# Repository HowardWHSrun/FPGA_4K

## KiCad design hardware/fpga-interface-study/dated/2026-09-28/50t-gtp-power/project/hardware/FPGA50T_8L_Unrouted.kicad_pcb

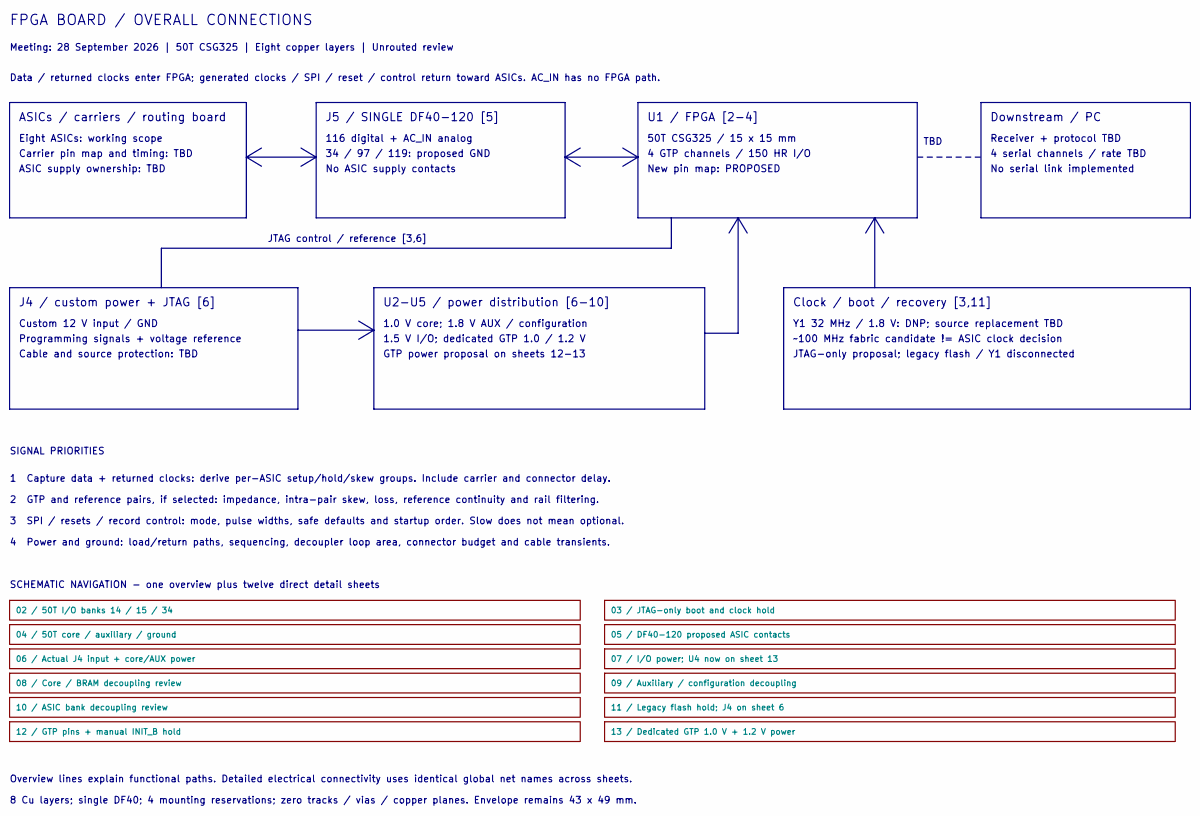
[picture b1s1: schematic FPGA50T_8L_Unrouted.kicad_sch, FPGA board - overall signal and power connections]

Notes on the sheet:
FPGA BOARD / OVERALL CONNECTIONS
Meeting: 28 September 2026 | 50T CSG325 | Eight copper layers | Unrouted review
Data / returned clocks enter FPGA; generated clocks / SPI / reset / control return toward ASICs. AC_IN has no FPGA path.
ASICs / carriers / routing board
Eight ASICs: working scope
Carrier pin map and timing: TBD
ASIC supply ownership: TBD
J5 / SINGLE DF40-120 [5]
116 digital + AC_IN analog
34 / 97 / 119: proposed GND
No ASIC supply contacts
U1 / FPGA [2-4]
50T CSG325 / 15 x 15 mm
4 GTP channels / 150 HR I/O
New pin map: PROPOSED
Downstream / PC
Receiver + protocol TBD
4 serial channels / rate TBD
No serial link implemented
TBD
J4 / custom power + JTAG [6]
Custom 12 V input / GND
Programming signals + voltage reference
Cable and source protection: TBD
U2-U5 / power distribution [6-10]
1.0 V core; 1.8 V AUX / configuration
1.5 V I/O; dedicated GTP 1.0 / 1.2 V
GTP power proposal on sheets 12-13
Clock / boot / recovery [3,11]
Y1 32 MHz / 1.8 V: DNP; source replacement TBD
~100 MHz fabric candidate != ASIC clock decision
JTAG-only proposal; legacy flash / Y1 disconnected
JTAG control / reference [3,6]
SIGNAL PRIORITIES
1 Capture data + returned clocks: derive per-ASIC setup/hold/skew groups. Include carrier and connector delay.
2 GTP and reference pairs, if selected: impedance, intra-pair skew, loss, reference continuity and rail filtering.
3 SPI / resets / record control: mode, pulse widths, safe defaults and startup order. Slow does not mean optional.
4 Power and ground: load/return paths, sequencing, decoupler loop area, connector budget and cable transients.
SCHEMATIC NAVIGATION - one overview plus twelve direct detail sheets
Overview lines explain functional paths. Detailed electrical connectivity uses identical global net names across sheets.

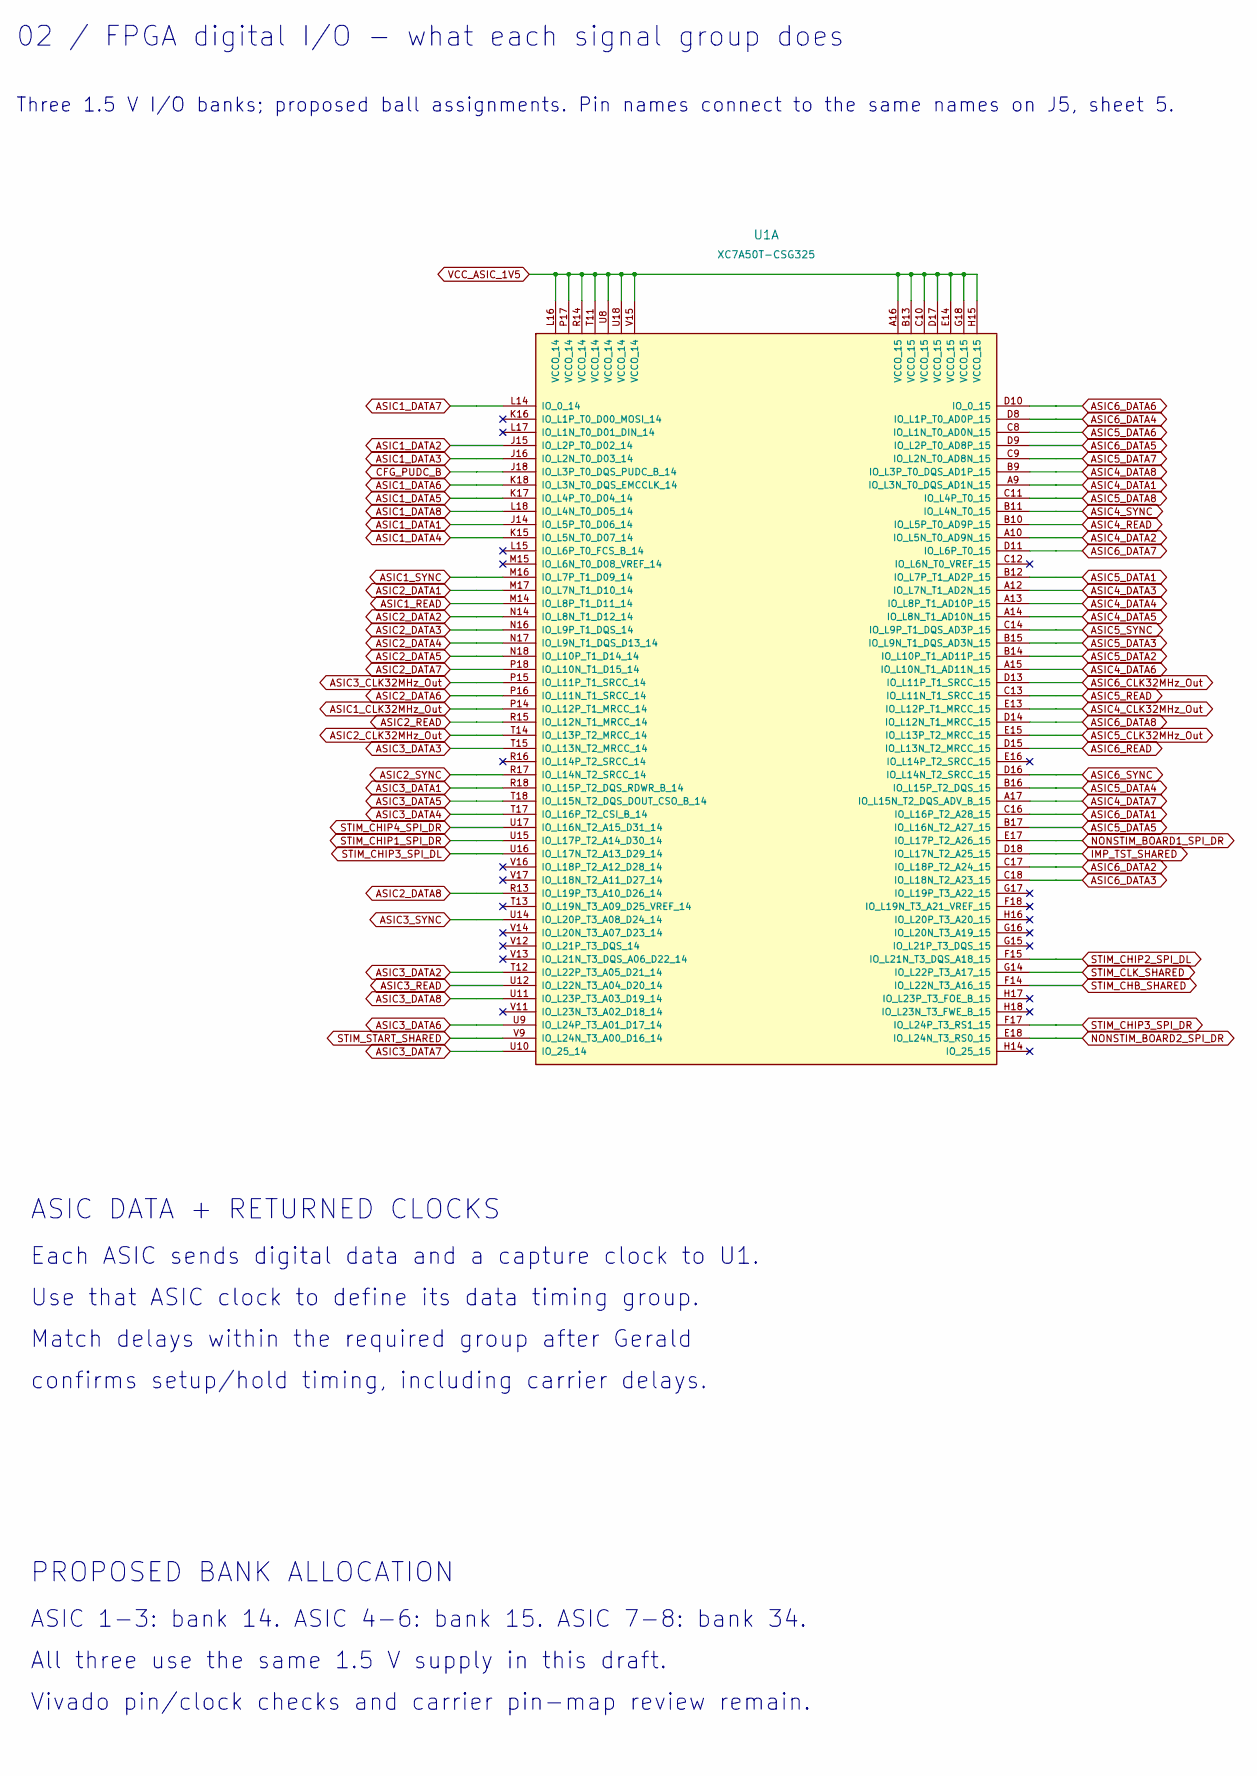
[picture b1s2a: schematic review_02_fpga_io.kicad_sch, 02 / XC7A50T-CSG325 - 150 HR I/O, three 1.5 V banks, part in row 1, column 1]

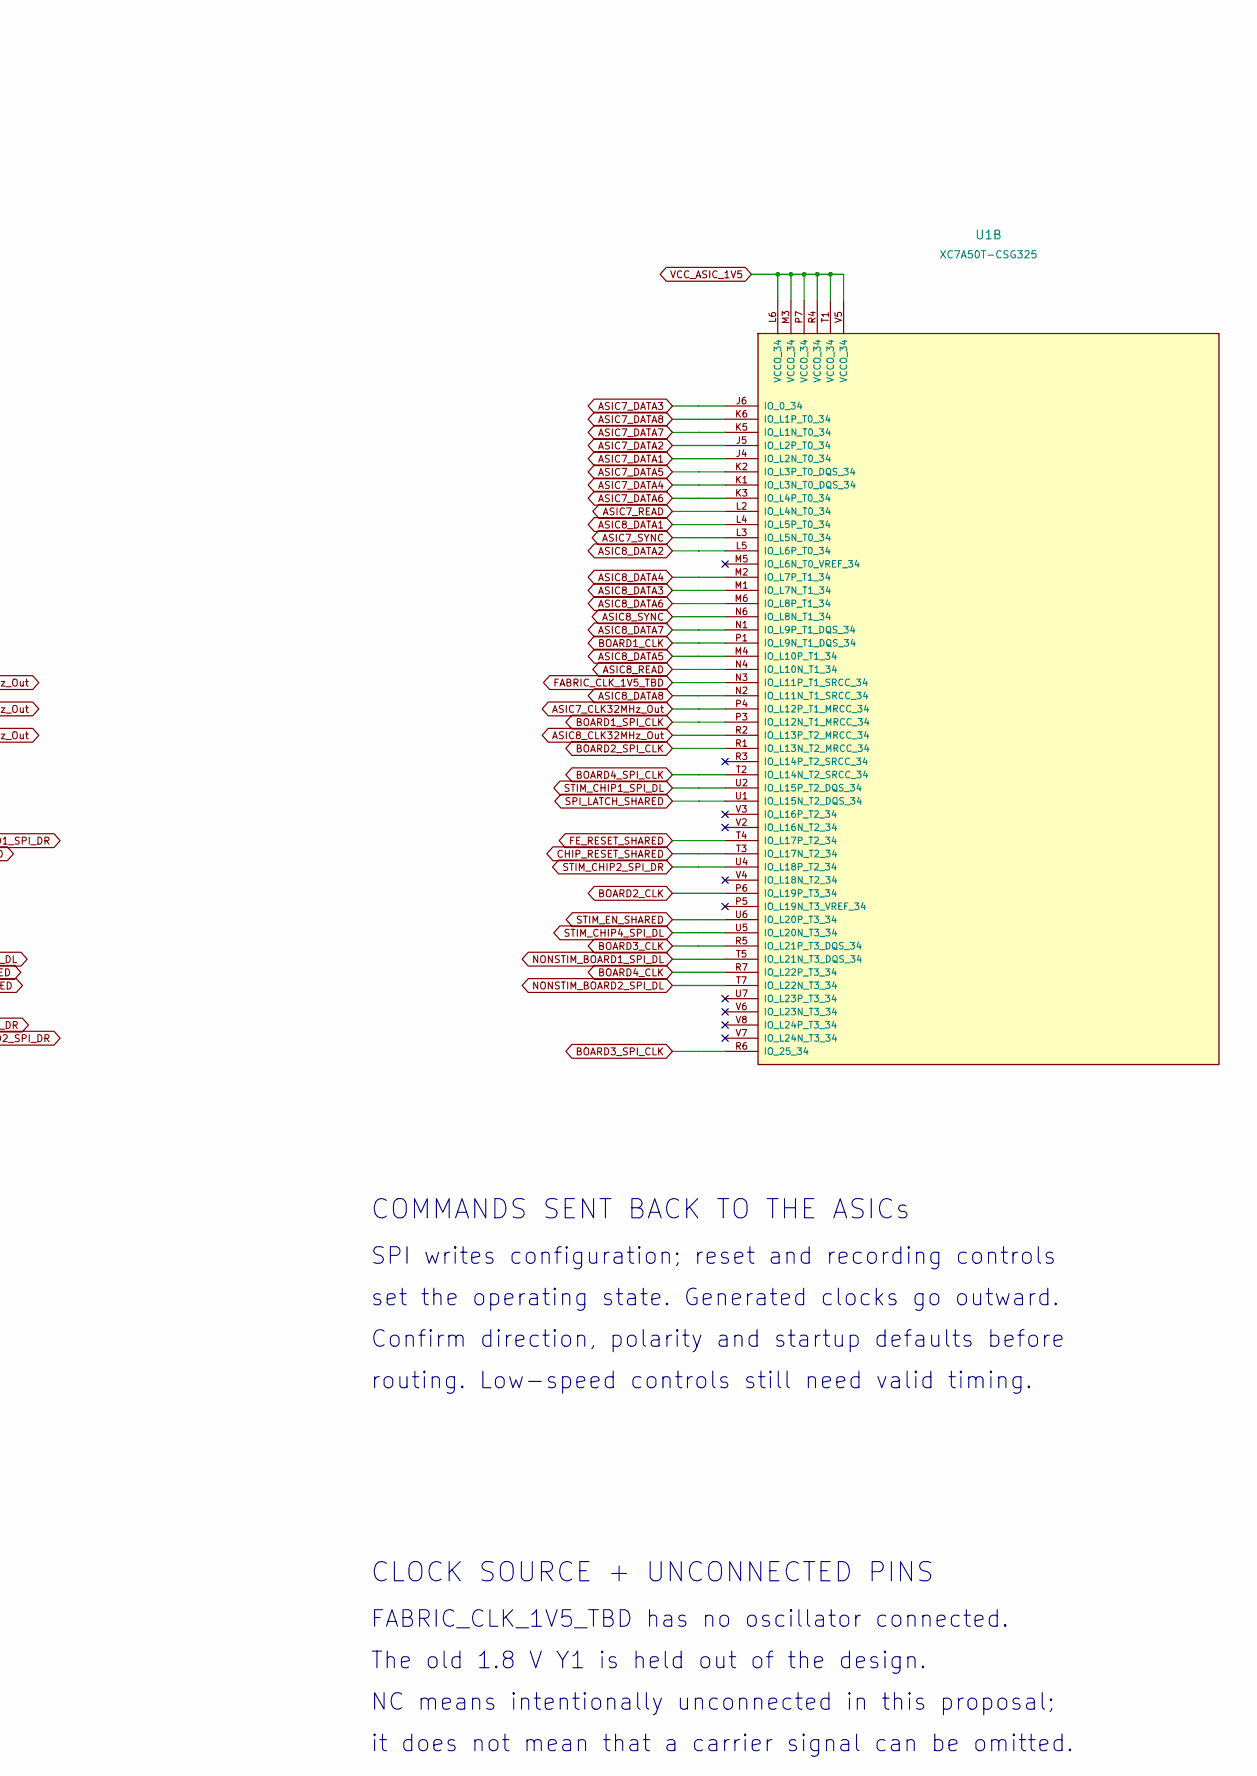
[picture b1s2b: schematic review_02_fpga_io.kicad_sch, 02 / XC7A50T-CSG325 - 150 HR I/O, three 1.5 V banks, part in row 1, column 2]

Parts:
U1: XC7A50T-CSG325; Xilinx_CSG325; MPN XC7A50T-CSG325; speed/temperature grade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

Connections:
ASIC1_CLK32MHz_Out: U1.P14 (IO_L12P_T1_MRCC_14); also elsewhere on the board
ASIC1_DATA1: U1.J14 (IO_L5P_T0_D06_14); also elsewhere on the board
ASIC1_DATA2: U1.J15 (IO_L2P_T0_D02_14); also elsewhere on the board
ASIC1_DATA3: U1.J16 (IO_L2N_T0_D03_14); also elsewhere on the board
ASIC1_DATA4: U1.K15 (IO_L5N_T0_D07_14); also elsewhere on the board
ASIC1_DATA5: U1.K17 (IO_L4P_T0_D04_14); also elsewhere on the board
ASIC1_DATA6: U1.K18 (IO_L3N_T0_DQS_EMCCLK_14); also elsewhere on the board
ASIC1_DATA7: U1.L14 (IO_0_14); also elsewhere on the board
ASIC1_DATA8: U1.L18 (IO_L4N_T0_D05_14); also elsewhere on the board
ASIC1_READ: U1.M14 (IO_L8P_T1_D11_14); also elsewhere on the board
ASIC1_SYNC: U1.M16 (IO_L7P_T1_D09_14); also elsewhere on the board
ASIC2_CLK32MHz_Out: U1.T14 (IO_L13P_T2_MRCC_14); also elsewhere on the board
ASIC2_DATA1: U1.M17 (IO_L7N_T1_D10_14); also elsewhere on the board
ASIC2_DATA2: U1.N14 (IO_L8N_T1_D12_14); also elsewhere on the board
ASIC2_DATA3: U1.N16 (IO_L9P_T1_DQS_14); also elsewhere on the board
ASIC2_DATA4: U1.N17 (IO_L9N_T1_DQS_D13_14); also elsewhere on the board
ASIC2_DATA5: U1.N18 (IO_L10P_T1_D14_14); also elsewhere on the board
ASIC2_DATA6: U1.P16 (IO_L11N_T1_SRCC_14); also elsewhere on the board
ASIC2_DATA7: U1.P18 (IO_L10N_T1_D15_14); also elsewhere on the board
ASIC2_DATA8: U1.R13 (IO_L19P_T3_A10_D26_14); also elsewhere on the board
ASIC2_READ: U1.R15 (IO_L12N_T1_MRCC_14); also elsewhere on the board
ASIC2_SYNC: U1.R17 (IO_L14N_T2_SRCC_14); also elsewhere on the board
ASIC3_CLK32MHz_Out: U1.P15 (IO_L11P_T1_SRCC_14); also elsewhere on the board
ASIC3_DATA1: U1.R18 (IO_L15P_T2_DQS_RDWR_B_14); also elsewhere on the board
ASIC3_DATA2: U1.T12 (IO_L22P_T3_A05_D21_14); also elsewhere on the board
ASIC3_DATA3: U1.T15 (IO_L13N_T2_MRCC_14); also elsewhere on the board
ASIC3_DATA4: U1.T17 (IO_L16P_T2_CSI_B_14); also elsewhere on the board
ASIC3_DATA5: U1.T18 (IO_L15N_T2_DQS_DOUT_CSO_B_14); also elsewhere on the board
ASIC3_DATA6: U1.U9 (IO_L24P_T3_A01_D17_14); also elsewhere on the board
ASIC3_DATA7: U1.U10 (IO_25_14); also elsewhere on the board
ASIC3_DATA8: U1.U11 (IO_L23P_T3_A03_D19_14); also elsewhere on the board
ASIC3_READ: U1.U12 (IO_L22N_T3_A04_D20_14); also elsewhere on the board
ASIC3_SYNC: U1.U14 (IO_L20P_T3_A08_D24_14); also elsewhere on the board
ASIC4_CLK32MHz_Out: U1.E13 (IO_L12P_T1_MRCC_15); also elsewhere on the board
ASIC4_DATA1: U1.A9 (IO_L3N_T0_DQS_AD1N_15); also elsewhere on the board
ASIC4_DATA2: U1.A10 (IO_L5N_T0_AD9N_15); also elsewhere on the board
ASIC4_DATA3: U1.A12 (IO_L7N_T1_AD2N_15); also elsewhere on the board
ASIC4_DATA4: U1.A13 (IO_L8P_T1_AD10P_15); also elsewhere on the board
ASIC4_DATA5: U1.A14 (IO_L8N_T1_AD10N_15); also elsewhere on the board
ASIC4_DATA6: U1.A15 (IO_L10N_T1_AD11N_15); also elsewhere on the board
ASIC4_DATA7: U1.A17 (IO_L15N_T2_DQS_ADV_B_15); also elsewhere on the board
ASIC4_DATA8: U1.B9 (IO_L3P_T0_DQS_AD1P_15); also elsewhere on the board
ASIC4_READ: U1.B10 (IO_L5P_T0_AD9P_15); also elsewhere on the board
ASIC4_SYNC: U1.B11 (IO_L4N_T0_15); also elsewhere on the board
ASIC5_CLK32MHz_Out: U1.E15 (IO_L13P_T2_MRCC_15); also elsewhere on the board
ASIC5_DATA1: U1.B12 (IO_L7P_T1_AD2P_15); also elsewhere on the board
ASIC5_DATA2: U1.B14 (IO_L10P_T1_AD11P_15); also elsewhere on the board
ASIC5_DATA3: U1.B15 (IO_L9N_T1_DQS_AD3N_15); also elsewhere on the board
ASIC5_DATA4: U1.B16 (IO_L15P_T2_DQS_15); also elsewhere on the board
ASIC5_DATA5: U1.B17 (IO_L16N_T2_A27_15); also elsewhere on the board
ASIC5_DATA6: U1.C8 (IO_L1N_T0_AD0N_15); also elsewhere on the board
ASIC5_DATA7: U1.C9 (IO_L2N_T0_AD8N_15); also elsewhere on the board
ASIC5_DATA8: U1.C11 (IO_L4P_T0_15); also elsewhere on the board
ASIC5_READ: U1.C13 (IO_L11N_T1_SRCC_15); also elsewhere on the board
ASIC5_SYNC: U1.C14 (IO_L9P_T1_DQS_AD3P_15); also elsewhere on the board
ASIC6_CLK32MHz_Out: U1.D13 (IO_L11P_T1_SRCC_15); also elsewhere on the board
ASIC6_DATA1: U1.C16 (IO_L16P_T2_A28_15); also elsewhere on the board
ASIC6_DATA2: U1.C17 (IO_L18P_T2_A24_15); also elsewhere on the board
ASIC6_DATA3: U1.C18 (IO_L18N_T2_A23_15); also elsewhere on the board
ASIC6_DATA4: U1.D8 (IO_L1P_T0_AD0P_15); also elsewhere on the board
ASIC6_DATA5: U1.D9 (IO_L2P_T0_AD8P_15); also elsewhere on the board
ASIC6_DATA6: U1.D10 (IO_0_15); also elsewhere on the board
ASIC6_DATA7: U1.D11 (IO_L6P_T0_15); also elsewhere on the board
ASIC6_DATA8: U1.D14 (IO_L12N_T1_MRCC_15); also elsewhere on the board
ASIC6_READ: U1.D15 (IO_L13N_T2_MRCC_15); also elsewhere on the board
ASIC6_SYNC: U1.D16 (IO_L14N_T2_SRCC_15); also elsewhere on the board
ASIC7_CLK32MHz_Out: U1.P4 (IO_L12P_T1_MRCC_34); also elsewhere on the board
ASIC7_DATA1: U1.J4 (IO_L2N_T0_34); also elsewhere on the board
ASIC7_DATA2: U1.J5 (IO_L2P_T0_34); also elsewhere on the board
ASIC7_DATA3: U1.J6 (IO_0_34); also elsewhere on the board
ASIC7_DATA4: U1.K1 (IO_L3N_T0_DQS_34); also elsewhere on the board
ASIC7_DATA5: U1.K2 (IO_L3P_T0_DQS_34); also elsewhere on the board
ASIC7_DATA6: U1.K3 (IO_L4P_T0_34); also elsewhere on the board
ASIC7_DATA7: U1.K5 (IO_L1N_T0_34); also elsewhere on the board
ASIC7_DATA8: U1.K6 (IO_L1P_T0_34); also elsewhere on the board
ASIC7_READ: U1.L2 (IO_L4N_T0_34); also elsewhere on the board
ASIC7_SYNC: U1.L3 (IO_L5N_T0_34); also elsewhere on the board
ASIC8_CLK32MHz_Out: U1.R2 (IO_L13P_T2_MRCC_34); also elsewhere on the board
ASIC8_DATA1: U1.L4 (IO_L5P_T0_34); also elsewhere on the board
ASIC8_DATA2: U1.L5 (IO_L6P_T0_34); also elsewhere on the board
ASIC8_DATA3: U1.M1 (IO_L7N_T1_34); also elsewhere on the board
ASIC8_DATA4: U1.M2 (IO_L7P_T1_34); also elsewhere on the board
ASIC8_DATA5: U1.M4 (IO_L10P_T1_34); also elsewhere on the board
ASIC8_DATA6: U1.M6 (IO_L8P_T1_34); also elsewhere on the board
ASIC8_DATA7: U1.N1 (IO_L9P_T1_DQS_34); also elsewhere on the board
ASIC8_DATA8: U1.N2 (IO_L11N_T1_SRCC_34); also elsewhere on the board
ASIC8_READ: U1.N4 (IO_L10N_T1_34); also elsewhere on the board
ASIC8_SYNC: U1.N6 (IO_L8N_T1_34); also elsewhere on the board
BOARD1_CLK: U1.P1 (IO_L9N_T1_DQS_34); also elsewhere on the board
BOARD1_SPI_CLK: U1.P3 (IO_L12N_T1_MRCC_34); also elsewhere on the board
BOARD2_CLK: U1.P6 (IO_L19P_T3_34); also elsewhere on the board
BOARD2_SPI_CLK: U1.R1 (IO_L13N_T2_MRCC_34); also elsewhere on the board
BOARD3_CLK: U1.R5 (IO_L21P_T3_DQS_34); also elsewhere on the board
BOARD3_SPI_CLK: U1.R6 (IO_25_34); also elsewhere on the board
BOARD4_CLK: U1.R7 (IO_L22P_T3_34); also elsewhere on the board
BOARD4_SPI_CLK: U1.T2 (IO_L14N_T2_SRCC_34); also elsewhere on the board
CFG_PUDC_B: U1.J18 (IO_L3P_T0_DQS_PUDC_B_14); also elsewhere on the board
CHIP_RESET_SHARED: U1.T3 (IO_L17N_T2_34); also elsewhere on the board
FABRIC_CLK_1V5_TBD: U1.N3 (IO_L11P_T1_SRCC_34)
FE_RESET_SHARED: U1.T4 (IO_L17P_T2_34); also elsewhere on the board
IMP_TST_SHARED: U1.D18 (IO_L17N_T2_A25_15); also elsewhere on the board
NONSTIM_BOARD1_SPI_DL: U1.T5 (IO_L21N_T3_DQS_34); also elsewhere on the board
NONSTIM_BOARD1_SPI_DR: U1.E17 (IO_L17P_T2_A26_15); also elsewhere on the board
NONSTIM_BOARD2_SPI_DL: U1.T7 (IO_L22N_T3_34); also elsewhere on the board
NONSTIM_BOARD2_SPI_DR: U1.E18 (IO_L24N_T3_RS0_15); also elsewhere on the board
SPI_LATCH_SHARED: U1.U1 (IO_L15N_T2_DQS_34); also elsewhere on the board
STIM_CHB_SHARED: U1.F14 (IO_L22N_T3_A16_15); also elsewhere on the board
STIM_CHIP1_SPI_DL: U1.U2 (IO_L15P_T2_DQS_34); also elsewhere on the board
STIM_CHIP1_SPI_DR: U1.U15 (IO_L17P_T2_A14_D30_14); also elsewhere on the board
STIM_CHIP2_SPI_DL: U1.F15 (IO_L21N_T3_DQS_A18_15); also elsewhere on the board
STIM_CHIP2_SPI_DR: U1.U4 (IO_L18P_T2_34); also elsewhere on the board
STIM_CHIP3_SPI_DL: U1.U16 (IO_L17N_T2_A13_D29_14); also elsewhere on the board
STIM_CHIP3_SPI_DR: U1.F17 (IO_L24P_T3_RS1_15); also elsewhere on the board
STIM_CHIP4_SPI_DL: U1.U5 (IO_L20N_T3_34); also elsewhere on the board
STIM_CHIP4_SPI_DR: U1.U17 (IO_L16N_T2_A15_D31_14); also elsewhere on the board
STIM_CLK_SHARED: U1.G14 (IO_L22P_T3_A17_15); also elsewhere on the board
STIM_EN_SHARED: U1.U6 (IO_L20P_T3_34); also elsewhere on the board
STIM_START_SHARED: U1.V9 (IO_L24N_T3_A00_D16_14); also elsewhere on the board
VCC_ASIC_1V5: U1.A16 (VCCO_15), U1.B13 (VCCO_15), U1.C10 (VCCO_15), U1.D17 (VCCO_15), U1.E14 (VCCO_15), U1.G18 (VCCO_15), U1.H15 (VCCO_15), U1.L6 (VCCO_34), U1.L16 (VCCO_14), U1.M3 (VCCO_34), U1.P7 (VCCO_34), U1.P17 (VCCO_14), U1.R4 (VCCO_34), U1.R14 (VCCO_14), U1.T1 (VCCO_34), U1.T11 (VCCO_14), U1.U8 (VCCO_14), U1.U18 (VCCO_14), U1.V5 (VCCO_34), U1.V15 (VCCO_14); also elsewhere on the board

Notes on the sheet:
02 / FPGA digital I/O - what each signal group does
Three 1.5 V I/O banks; proposed ball assignments. Pin names connect to the same names on J5, sheet 5.
ASIC DATA + RETURNED CLOCKS
Each ASIC sends digital data and a capture clock to U1.
Use that ASIC clock to define its data timing group.
Match delays within the required group after Gerald
confirms setup/hold timing, including carrier delays.
COMMANDS SENT BACK TO THE ASICs
SPI writes configuration; reset and recording controls
set the operating state. Generated clocks go outward.
Confirm direction, polarity and startup defaults before
routing. Low-speed controls still need valid timing.
PROPOSED BANK ALLOCATION
ASIC 1-3: bank 14. ASIC 4-6: bank 15. ASIC 7-8: bank 34.
All three use the same 1.5 V supply in this draft.
Vivado pin/clock checks and carrier pin-map review remain.
CLOCK SOURCE + UNCONNECTED PINS
FABRIC_CLK_1V5_TBD has no oscillator connected.
The old 1.8 V Y1 is held out of the design.
NC means intentionally unconnected in this proposal;
it does not mean that a carrier signal can be omitted.

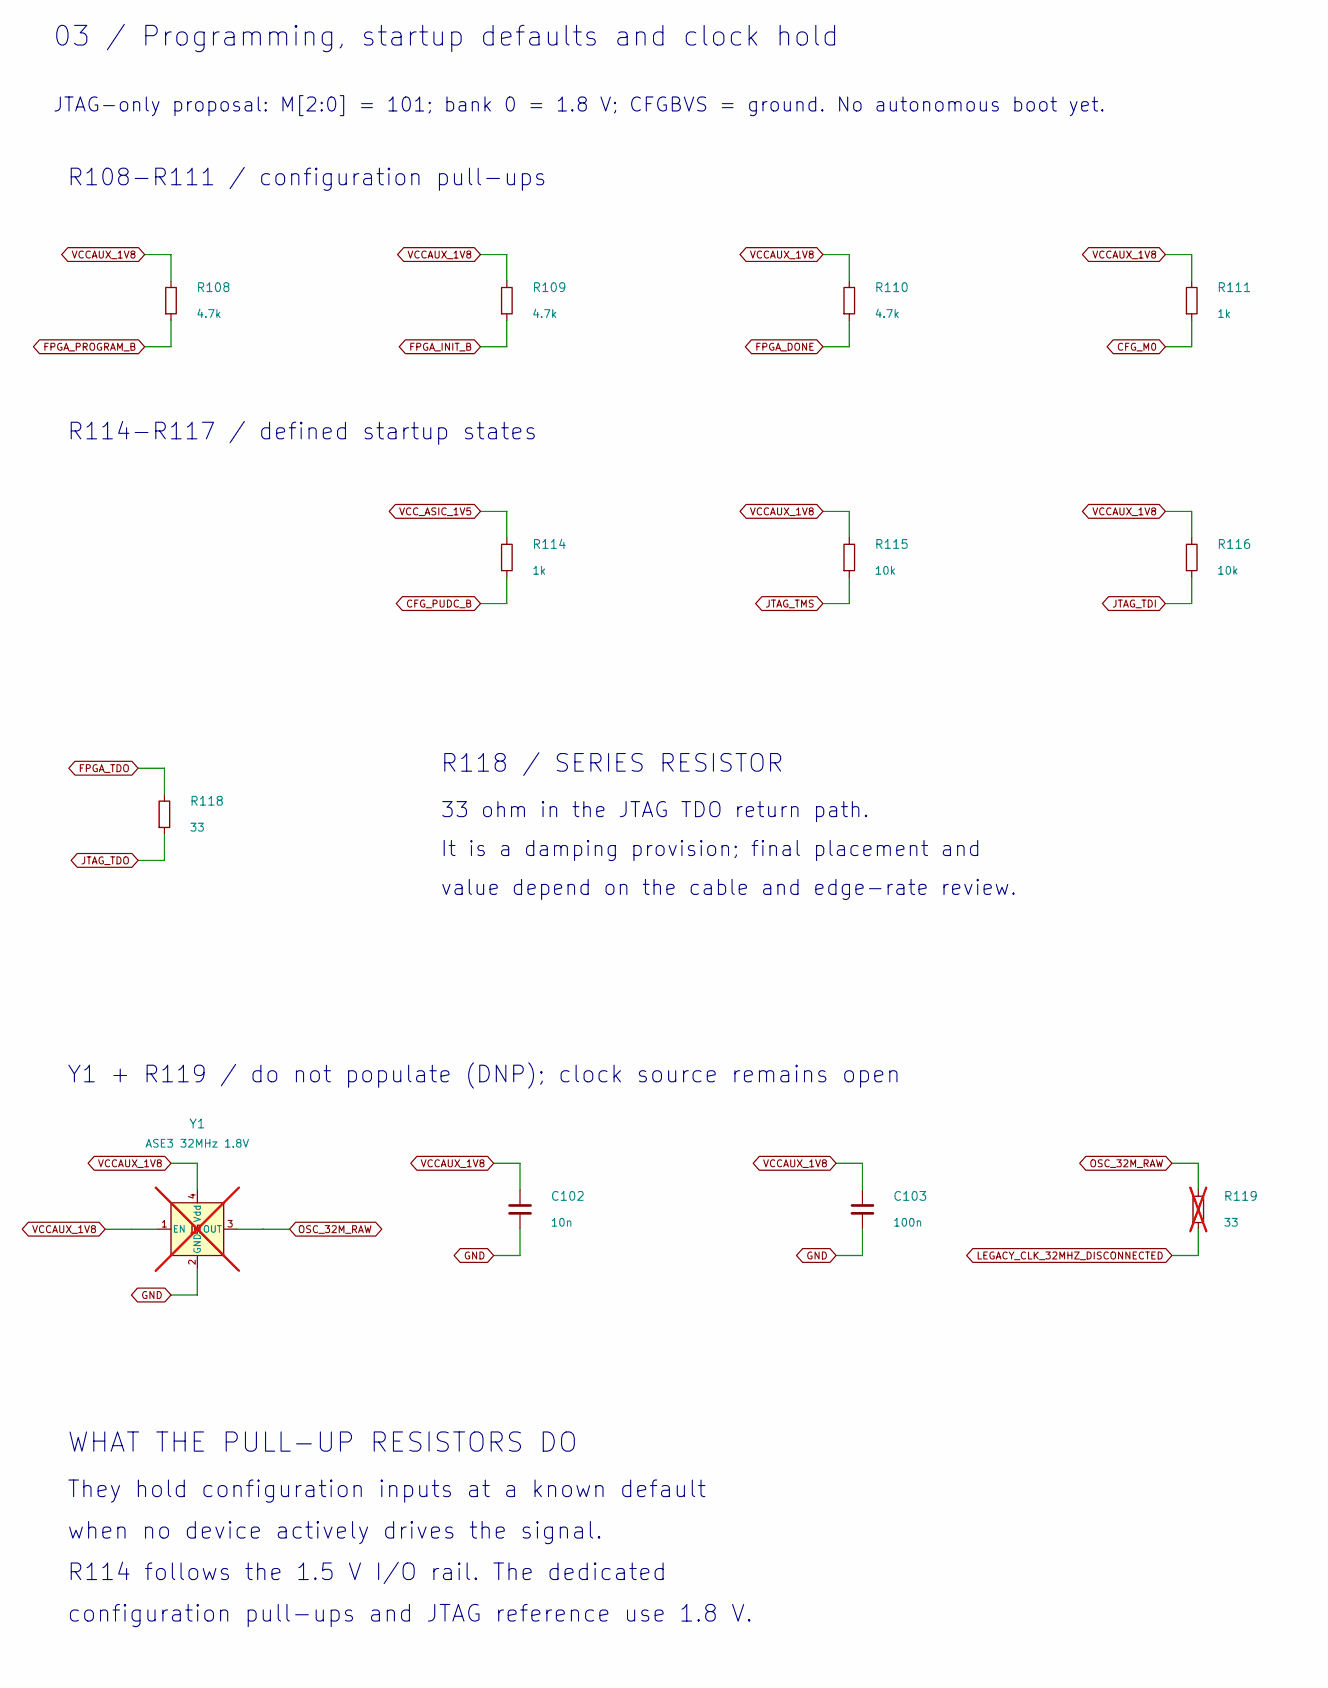
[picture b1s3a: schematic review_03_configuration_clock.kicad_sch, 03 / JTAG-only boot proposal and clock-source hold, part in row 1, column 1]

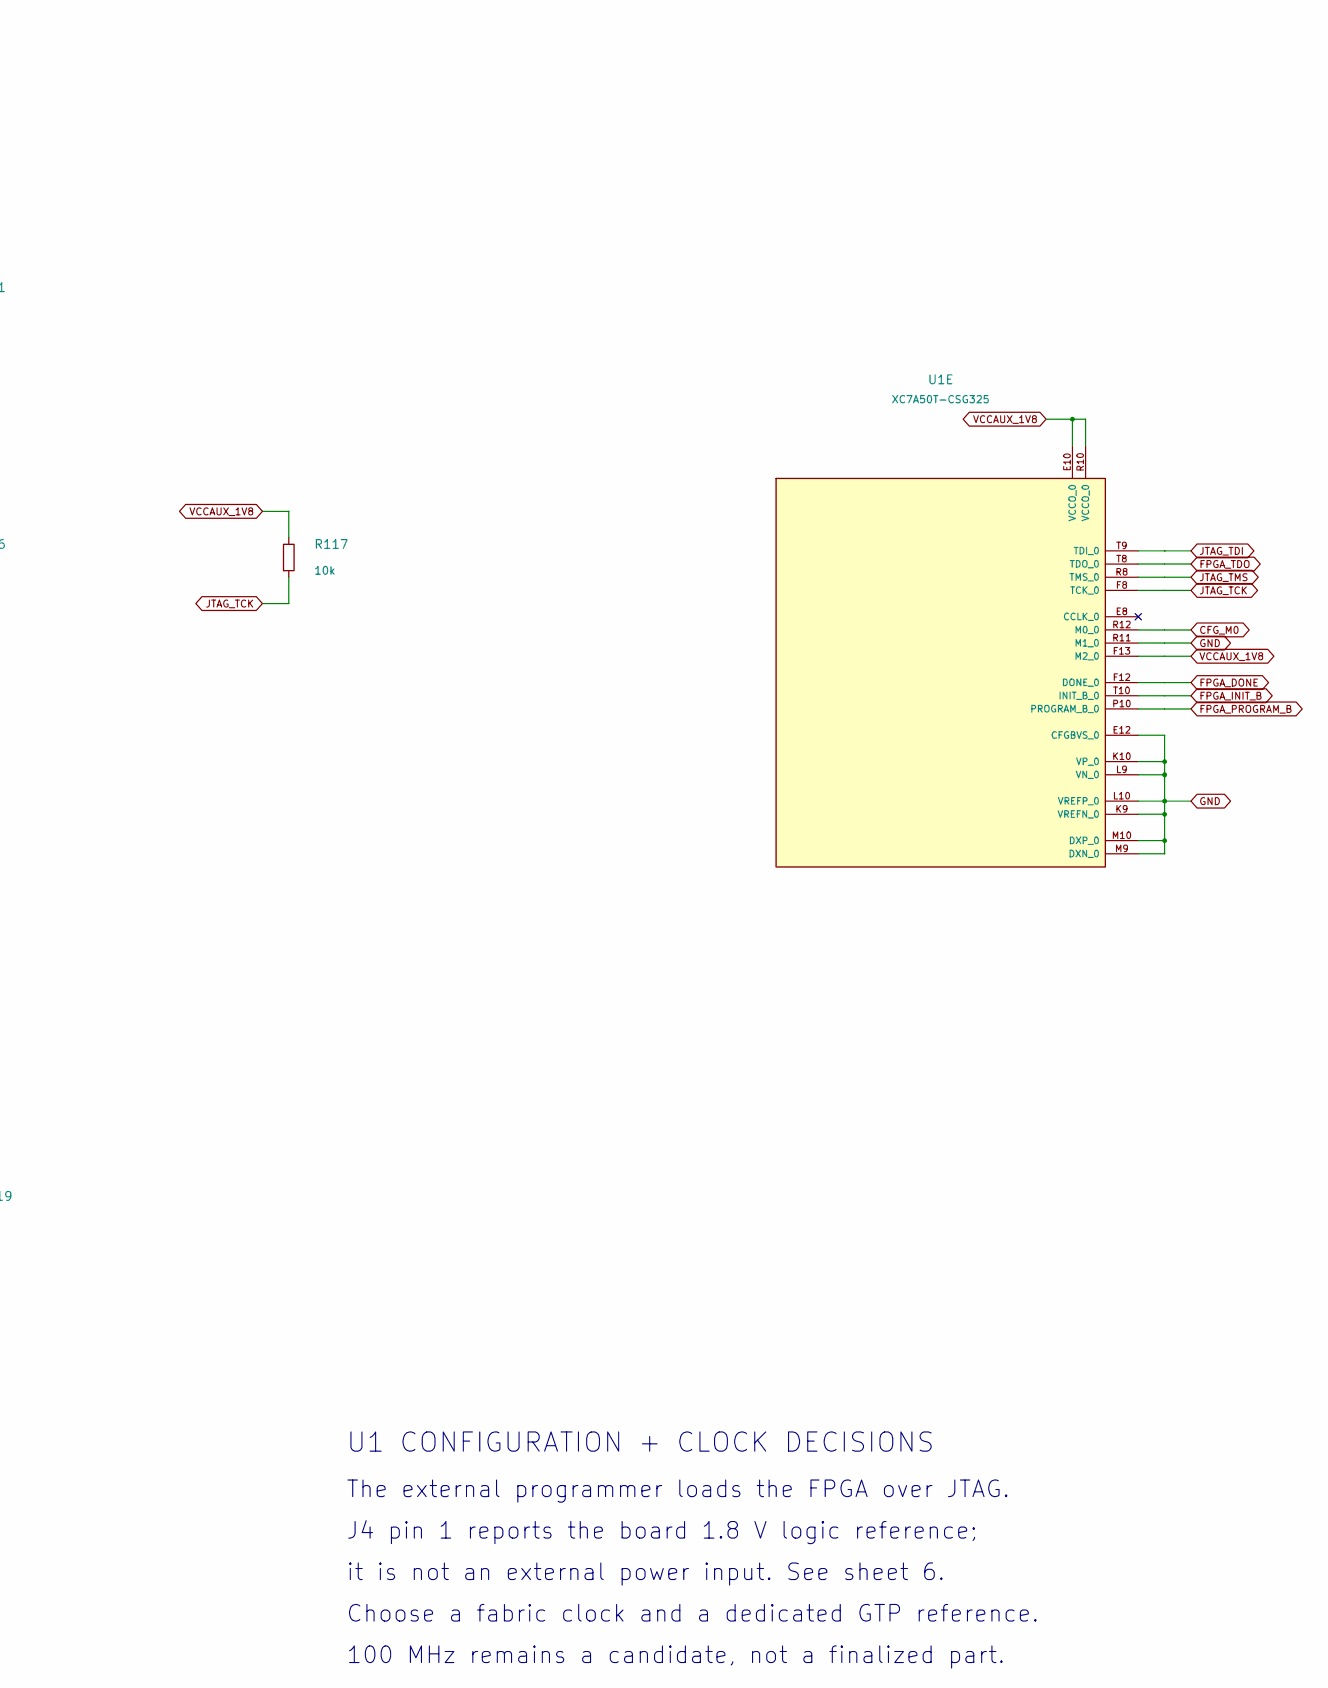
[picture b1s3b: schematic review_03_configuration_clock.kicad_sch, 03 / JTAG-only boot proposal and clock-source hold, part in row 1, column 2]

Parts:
C102: 10n; Capacitor_SMD__C_0402_1005Metric; MPN GRM155R71C103KA01D
C103: 100n; Capacitor_SMD__C_0402_1005Metric; MPN GRM155R71C104KA88D
R108, R109, R110: 4.7k; Resistor_SMD__R_0402_1005Metric; MPN CRCW04024K70FKED
R111, R114: 1k; Resistor_SMD__R_0402_1005Metric; MPN CRCW04021K00FKED
R115, R116, R117: 10k; Resistor_SMD__R_0402_1005Metric; MPN CRCW040210K0FKED
R118: 33; Resistor_SMD__R_0402_1005Metric; MPN CRCW040233R0FKED
R119: 33; Resistor_SMD__R_0402_1005Metric; MPN CRCW040233R0FKED; not fitted
U1: XC7A50T-CSG325; Xilinx_CSG325; MPN XC7A50T-CSG325; speed/temperature grade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
Y1: ASE3 32MHz 1.8V; Oscillator__Oscillator_SMD_Abracon_ASE-4Pin_3_2x2_5mm; MPN ASE3-32.000MHZ-L-C-T; not fitted

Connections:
CFG_M0: R111.2, U1.R12 (M0_0)
CFG_PUDC_B: R114.2; also elsewhere on the board
FPGA_DONE: R110.2, U1.F12 (DONE_0)
FPGA_INIT_B: R109.2, U1.T10 (INIT_B_0); also elsewhere on the board
FPGA_PROGRAM_B: R108.2, U1.P10 (PROGRAM_B_0)
FPGA_TDO: R118.1, U1.T8 (TDO_0)
GND: C102.2, C103.2, U1.E12 (CFGBVS_0), U1.K9 (VREFN_0), U1.K10 (VP_0), U1.L9 (VN_0), U1.L10 (VREFP_0), U1.M9 (DXN_0), U1.M10 (DXP_0), U1.R11 (M1_0), Y1.2 (GND); also elsewhere on the board
JTAG_TCK: R117.2, U1.F8 (TCK_0); also elsewhere on the board
JTAG_TDI: R116.2, U1.T9 (TDI_0); also elsewhere on the board
JTAG_TDO: R118.2; also elsewhere on the board
JTAG_TMS: R115.2, U1.R8 (TMS_0); also elsewhere on the board
LEGACY_CLK_32MHZ_DISCONNECTED: R119.2
OSC_32M_RAW: R119.1, Y1.3 (OUT)
VCCAUX_1V8: C102.1, C103.1, R108.1, R109.1, R110.1, R111.1, R115.1, R116.1, R117.1, U1.E10 (VCCO_0), U1.F13 (M2_0), U1.R10 (VCCO_0), Y1.1 (EN), Y1.4 (Vdd); also elsewhere on the board
VCC_ASIC_1V5: R114.1; also elsewhere on the board

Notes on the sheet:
03 / Programming, startup defaults and clock hold
JTAG-only proposal: M[2:0] = 101; bank 0 = 1.8 V; CFGBVS = ground. No autonomous boot yet.
R108-R111 / configuration pull-ups
R114-R117 / defined startup states
R118 / SERIES RESISTOR
33 ohm in the JTAG TDO return path.
It is a damping provision; final placement and
value depend on the cable and edge-rate review.
Y1 + R119 / do not populate (DNP); clock source remains open
WHAT THE PULL-UP RESISTORS DO
They hold configuration inputs at a known default
when no device actively drives the signal.
R114 follows the 1.5 V I/O rail. The dedicated
configuration pull-ups and JTAG reference use 1.8 V.
U1 CONFIGURATION + CLOCK DECISIONS
The external programmer loads the FPGA over JTAG.
J4 pin 1 reports the board 1.8 V logic reference;
it is not an external power input. See sheet 6.
Choose a fabric clock and a dedicated GTP reference.
100 MHz remains a candidate, not a finalized part.

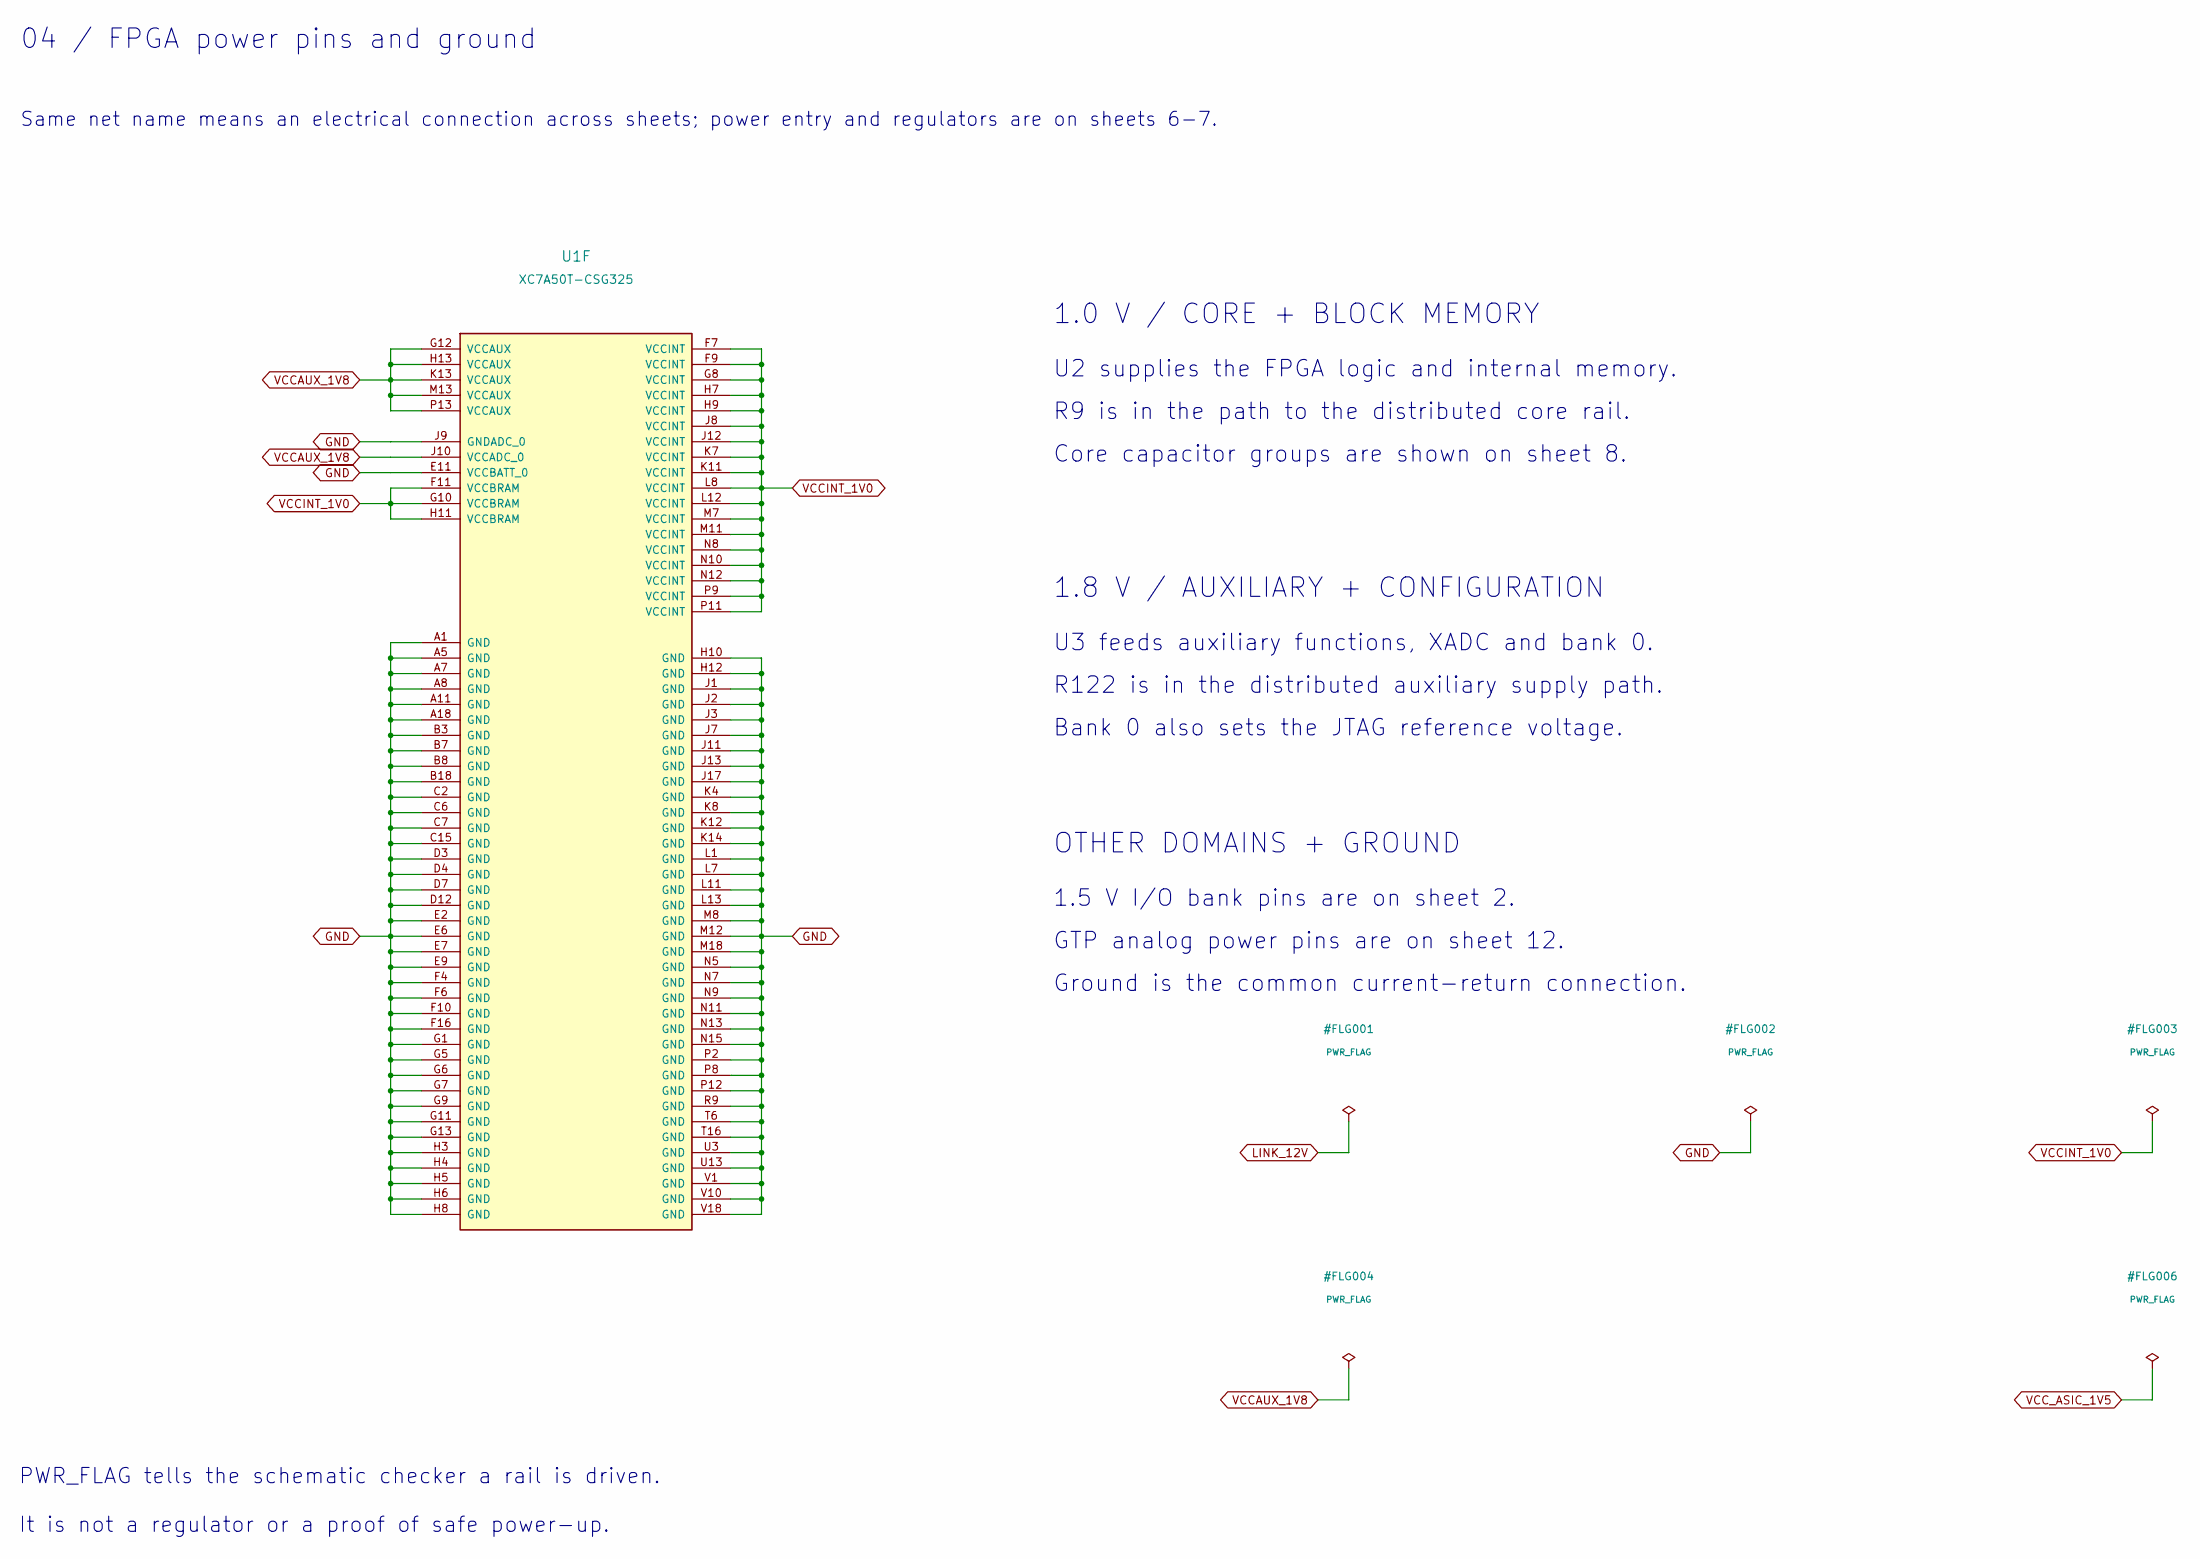
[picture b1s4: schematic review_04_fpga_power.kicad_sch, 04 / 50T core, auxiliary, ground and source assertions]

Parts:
U1: XC7A50T-CSG325; Xilinx_CSG325; MPN XC7A50T-CSG325; speed/temperature grade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

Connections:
GND: U1.A1 (GND), U1.A5 (GND), U1.A7 (GND), U1.A8 (GND), U1.A11 (GND), U1.A18 (GND), U1.B3 (GND), U1.B7 (GND), U1.B8 (GND), U1.B18 (GND), U1.C2 (GND), U1.C6 (GND), U1.C7 (GND), U1.C15 (GND), U1.D3 (GND), U1.D4 (GND), U1.D7 (GND), U1.D12 (GND), U1.E2 (GND), U1.E6 (GND), U1.E7 (GND), U1.E9 (GND), U1.E11 (VCCBATT_0), U1.F4 (GND), U1.F6 (GND), U1.F10 (GND), U1.F16 (GND), U1.G1 (GND), U1.G5 (GND), U1.G6 (GND), U1.G7 (GND), U1.G9 (GND), U1.G11 (GND), U1.G13 (GND), U1.H3 (GND), U1.H4 (GND), U1.H5 (GND), U1.H6 (GND), U1.H8 (GND), U1.H10 (GND), U1.H12 (GND), U1.J1 (GND), U1.J2 (GND), U1.J3 (GND), U1.J7 (GND), U1.J9 (GNDADC_0), U1.J11 (GND), U1.J13 (GND), U1.J17 (GND), U1.K4 (GND), U1.K8 (GND), U1.K12 (GND), U1.K14 (GND), U1.L1 (GND), U1.L7 (GND), U1.L11 (GND), U1.L13 (GND), U1.M8 (GND), U1.M12 (GND), U1.M18 (GND), U1.N5 (GND), U1.N7 (GND), U1.N9 (GND), U1.N11 (GND), U1.N13 (GND), U1.N15 (GND), U1.P2 (GND), U1.P8 (GND), U1.P12 (GND), U1.R9 (GND), U1.T6 (GND), U1.T16 (GND), U1.U3 (GND), U1.U13 (GND), U1.V1 (GND), U1.V10 (GND), U1.V18 (GND); also elsewhere on the board
VCCAUX_1V8: U1.G12 (VCCAUX), U1.H13 (VCCAUX), U1.J10 (VCCADC_0), U1.K13 (VCCAUX), U1.M13 (VCCAUX), U1.P13 (VCCAUX); also elsewhere on the board
VCCINT_1V0: U1.F7 (VCCINT), U1.F9 (VCCINT), U1.F11 (VCCBRAM), U1.G8 (VCCINT), U1.G10 (VCCBRAM), U1.H7 (VCCINT), U1.H9 (VCCINT), U1.H11 (VCCBRAM), U1.J8 (VCCINT), U1.J12 (VCCINT), U1.K7 (VCCINT), U1.K11 (VCCINT), U1.L8 (VCCINT), U1.L12 (VCCINT), U1.M7 (VCCINT), U1.M11 (VCCINT), U1.N8 (VCCINT), U1.N10 (VCCINT), U1.N12 (VCCINT), U1.P9 (VCCINT), U1.P11 (VCCINT); also elsewhere on the board

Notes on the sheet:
04 / FPGA power pins and ground
Same net name means an electrical connection across sheets; power entry and regulators are on sheets 6-7.
1.0 V / CORE + BLOCK MEMORY
U2 supplies the FPGA logic and internal memory.
R9 is in the path to the distributed core rail.
Core capacitor groups are shown on sheet 8.
1.8 V / AUXILIARY + CONFIGURATION
U3 feeds auxiliary functions, XADC and bank 0.
R122 is in the distributed auxiliary supply path.
Bank 0 also sets the JTAG reference voltage.
OTHER DOMAINS + GROUND
1.5 V I/O bank pins are on sheet 2.
GTP analog power pins are on sheet 12.
Ground is the common current-return connection.
PWR_FLAG tells the schematic checker a rail is driven.
It is not a regulator or a proof of safe power-up.
